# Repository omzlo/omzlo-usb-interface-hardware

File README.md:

These design files are provided for the Omzlo USB CAN controller, as part of the Omzlo open hardware platform.

For the firmware see https://github.com/omzlo/omzlo-usb-interface

For more details see http://omlzo.com/one

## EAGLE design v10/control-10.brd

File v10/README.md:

Here are the design files for the prototype version of the Omzlo USB controller, version 10.

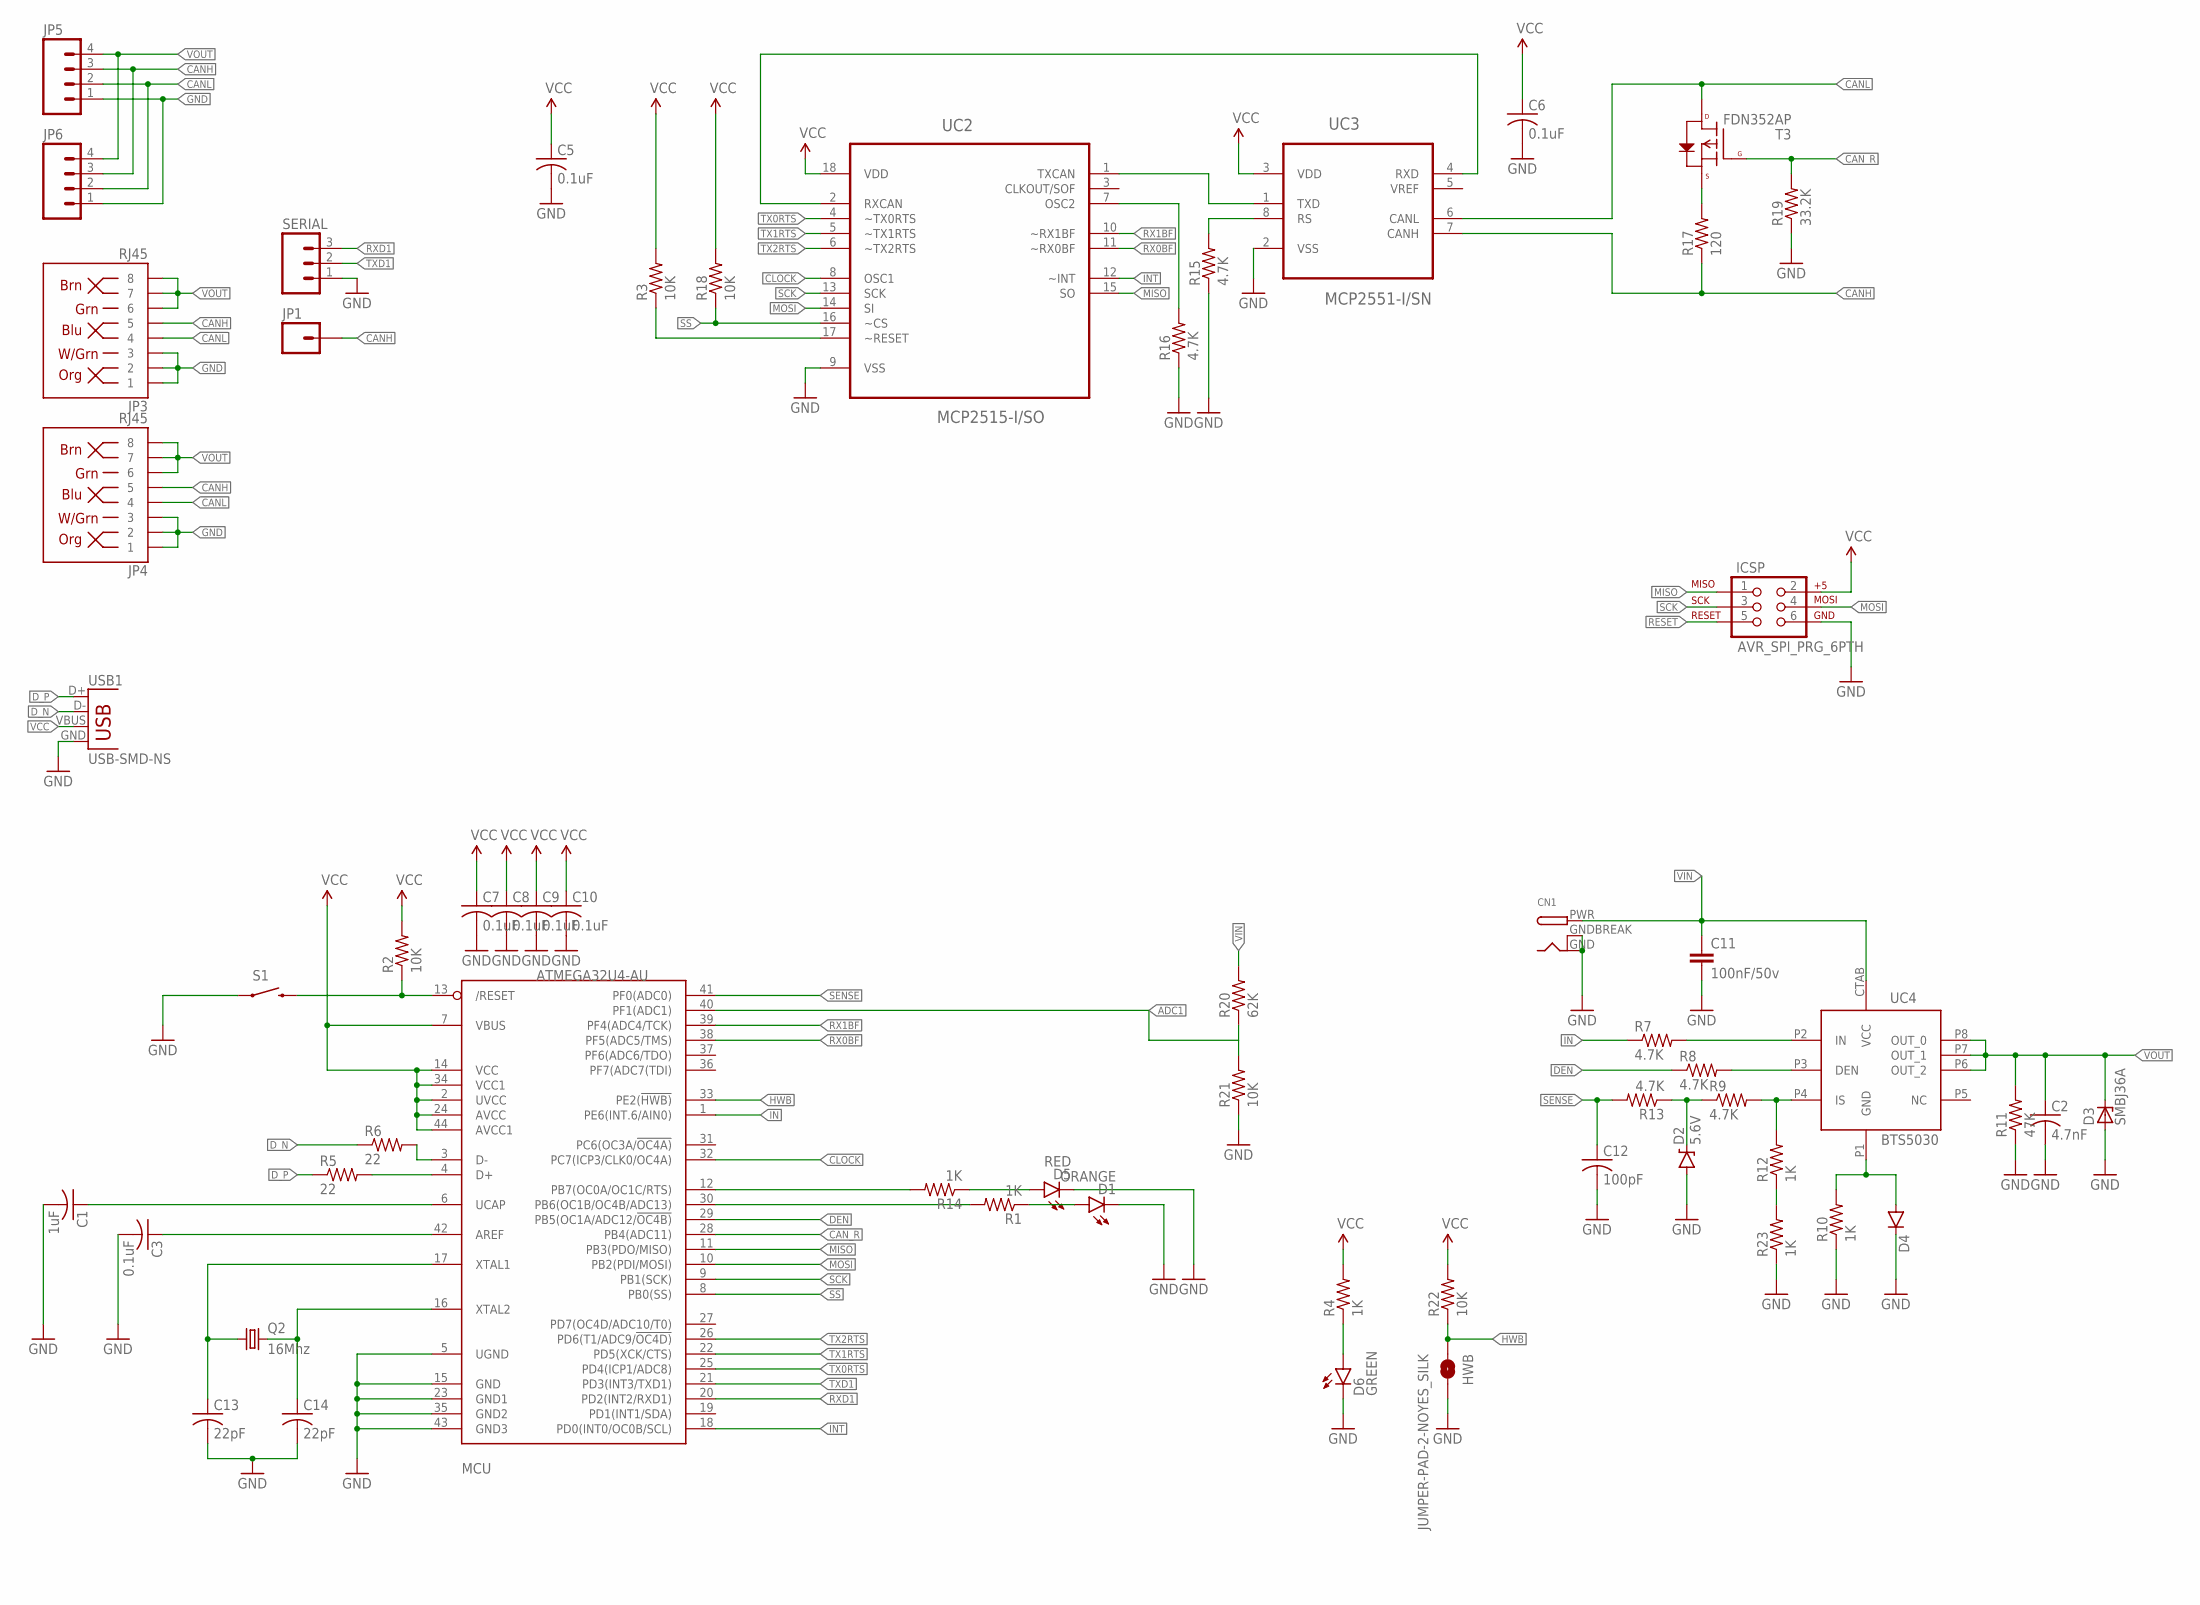
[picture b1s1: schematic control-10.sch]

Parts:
C1: 1uF; C0805
C2: 4.7nF; C0805
C3, C5, C6, C7, C8, C9, C10: 0.1uF; C0603
C11: 100nF/50v; 0805
C12: 100pF; C0805
C13, C14: 22pF; C0805
CN1: DCBARRELPTH; DCJACK_2MM_PTH
D1: ORANGE; LED-1206
D2: 5.6V; SOD-323
D3: SMBJ36A; SMB
D4: DIODESMA; SMA-DIODE
D5: RED; LED-1206
D6: GREEN; LED-1206
HWB: JUMPER-PAD-2-NOYES_SILK; PAD-JUMPER-2-NO_YES_SILK
ICSP: AVR_SPI_PRG_6PTH; 2X3
JP1: M01NOSILK-KIT; 1X01NS-KIT
JP3, JP4: RJ45; RJ45-8
JP5, JP6: M04SCREW; SCREWTERMINAL-3.5MM-4
MCU: ATMEGA32U4-AU; TQFP44
Q2: 16Mhz; HC49UP
R1, R4, R14: 1K; 0805
R2, R3, R18, R21, R22: 10K; M0805
R5, R6: 22; M0805
R7, R8, R9, R13, R15, R16: 4.7K; M0805
R10, R12, R23: 1K; M0805
R11: 47K; M0805
R17: 120; M0805
R19: 33.2K; M0805
R20: 62K; M0805
S1: SWITCH-MOMENTARY-2SMD-1101NE; TACTILE-SWITCH-1101NE
SERIAL: M03PTH; 1X03
T3: FDN352AP; SOT23-3
UC2: MCP2515-I/SO; SOIC127P1034X264-18N
UC3: MCP2551-I/SN; SOIC127P600X175-8N
UC4: BTS5030; PG-DSO-8-43
USB1: USB-SMD-NS; USB-MINIB-NOSTOP

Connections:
ADC1: MCU.40 (PF1(ADC1)), R20.1, R21.2
CANH: JP1.1, JP3.5, JP4.5, JP5.3, JP6.3, R17.1, UC3.7 (CANH)
CANL: JP3.4, JP4.4, JP5.2, JP6.2, T3.3 (D), UC3.6 (CANL)
CAN_R: MCU.28 (PB4(ADC11)), R19.2, T3.1 (G)
CLOCK: MCU.32 (PC7(ICP3/CLK0/OC4A)), UC2.8 (OSC1)
DEN: MCU.29 (PB5(OC1A/ADC12/!OC4B)), R8.1
DU_N: MCU.3 (D-), R6.2
DU_P: MCU.4 (D+), R5.2
D_N: R6.1, USB1.D-
D_P: R5.1, USB1.D+
GND: C1.2, C2.2, C3.2, C5.2, C6.2, C7.2, C8.2, C9.2, C10.2, C11.2, C12.2, C13.2, C14.2, CN1.GND, CN1.GNDBREAK, D1.C, D2.A, D3.A, D4.C, D5.C, D6.C, HWB.2, ICSP.6, JP3.1, JP3.2, JP3.3, JP4.1, JP4.2, JP4.3, JP5.1, JP6.1, MCU.5 (UGND), MCU.15 (GND), MCU.23 (GND1), MCU.35 (GND2), MCU.43 (GND3), R10.1, R11.1, R15.1, R16.1, R19.1, R21.1, R23.1, S1.1, SERIAL.1, UC2.9 (VSS), UC3.2 (VSS), USB1.GND
HWB: HWB.1, MCU.33 (PE2(!HWB)), R22.1
IN: MCU.1 (PE6(INT.6/AIN0)), R7.1
INT: MCU.18 (PD0(INT0/OC0B/SCL)), UC2.12 (~INT)
MISO: ICSP.1, MCU.11 (PB3(PDO/MISO)), UC2.15 (SO)
MOSI: ICSP.4, MCU.10 (PB2(PDI/MOSI)), UC2.14 (SI)
unnamed: C13.1, MCU.17 (XTAL1), Q2.1
unnamed: D1.A, R1.1
unnamed: R7.2, UC4.P2 (IN)
unnamed: UC2.1 (TXCAN), UC3.1 (TXD)
unnamed: C14.1, MCU.16 (XTAL2), Q2.2
unnamed: UC2.2 (RXCAN), UC3.4 (RXD)
unnamed: R16.2, UC2.7 (OSC2)
unnamed: R12.1, R23.2
unnamed: R3.1, UC2.17 (~RESET)
unnamed: R8.2, UC4.P3 (DEN)
unnamed: R15.2, UC3.8 (RS)
unnamed: R17.2, T3.2 (S)
unnamed: R9.2, R12.2, UC4.P4 (IS)
unnamed: D4.A, R10.2, UC4.P1 (GND)
unnamed: MCU.12 (PB7(OC0A/OC1C/RTS)), R14.2
unnamed: D2.C, R9.1, R13.1
unnamed: MCU.30 (PB6(OC1B/OC4B/ADC13)), R1.2
unnamed: D5.A, R14.1
unnamed: C3.1, MCU.42 (AREF)
unnamed: D6.A, R4.1
unnamed: C1.1, MCU.6 (UCAP)
RESET: ICSP.5, MCU.13 (/RESET), R2.1, S1.2
RX0BF: MCU.38 (PF5(ADC5/TMS)), UC2.11 (~RX0BF)
RX1BF: MCU.39 (PF4(ADC4/TCK)), UC2.10 (~RX1BF)
RXD1: MCU.20 (PD2(INT2/RXD1)), SERIAL.3
SCK: ICSP.3, MCU.9 (PB1(SCK)), UC2.13 (SCK)
SENSE: C12.1, MCU.41 (PF0(ADC0)), R13.2
SS: MCU.8 (PB0(SS)), R18.1, UC2.16 (~CS)
TX0RTS: MCU.25 (PD4(ICP1/ADC8)), UC2.4 (~TX0RTS)
TX1RTS: MCU.22 (PD5(XCK/CTS)), UC2.5 (~TX1RTS)
TX2RTS: MCU.26 (PD6(T1/ADC9/!OC4D)), UC2.6 (~TX2RTS)
TXD1: MCU.21 (PD3(INT3/TXD1)), SERIAL.2
VCC: C5.1, C6.1, C7.1, C8.1, C9.1, C10.1, ICSP.2, MCU.2 (UVCC), MCU.7 (VBUS), MCU.14 (VCC), MCU.24 (AVCC), MCU.34 (VCC1), MCU.44 (AVCC1), R2.2, R3.2, R4.2, R18.2, R22.2, UC2.18 (VDD), UC3.3 (VDD), USB1.VBUS
VIN: C11.1, CN1.PWR, R20.2, UC4.CTAB (VCC)
VOUT: C2.1, D3.C, JP3.6, JP3.7, JP3.8, JP4.6, JP4.7, JP4.8, JP5.4, JP6.4, R11.2, UC4.P6 (OUT_2), UC4.P7 (OUT_1), UC4.P8 (OUT_0)

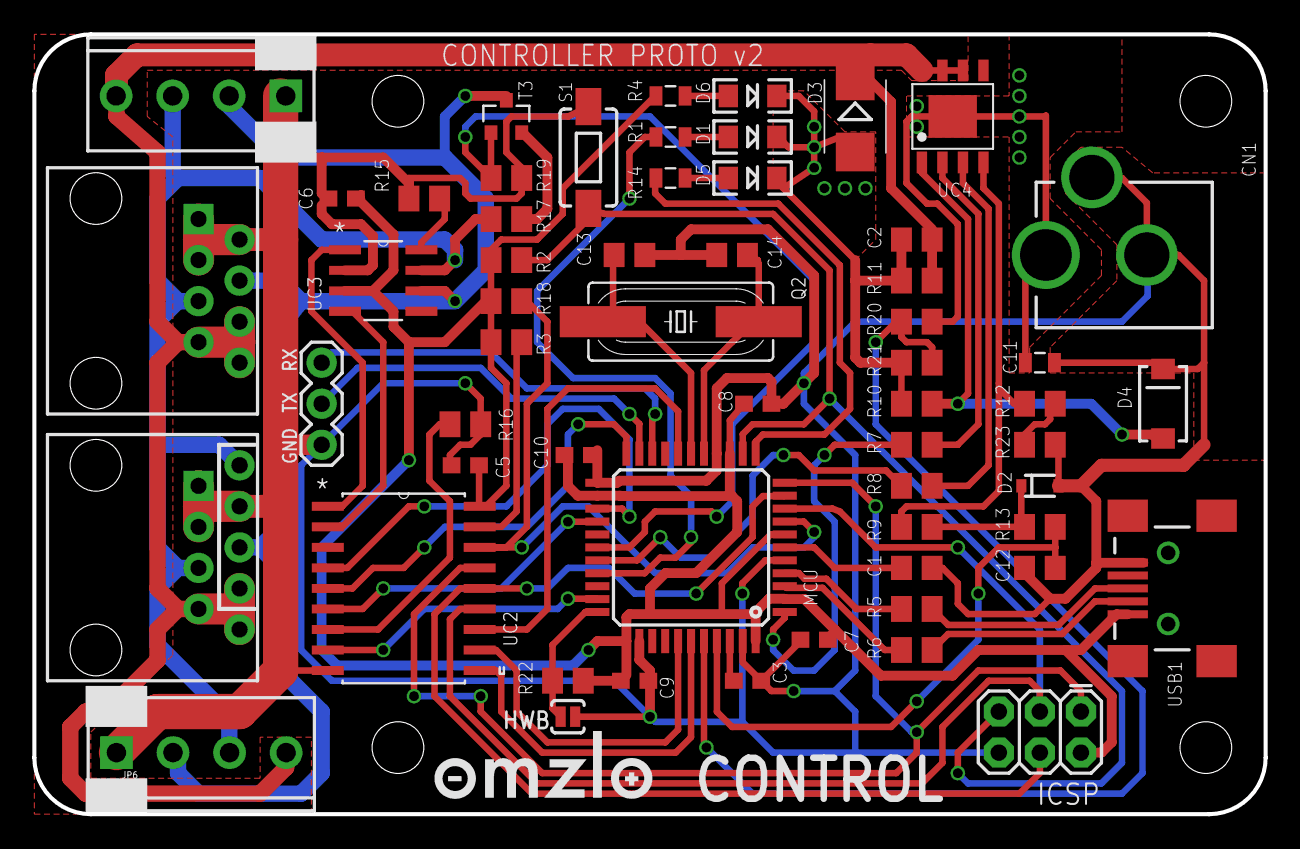
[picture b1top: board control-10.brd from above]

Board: 2 copper layers, 76.2 x 48.3 mm, 60 parts (0 on the bottom side), 51 nets.

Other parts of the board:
U$1: OMZLO-0.5

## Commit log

2017-03-13 Added schematics
2017-03-13 Create LICENSE
2017-03-23 Added Eagle design files
2017-03-23 Add Eagle board files

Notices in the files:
parts and their libraries:
SparkFun-LED: Licensing: Creative Commons ShareAlike 4.0 International - https://creativecommons.org/licenses/by-sa/4.0
